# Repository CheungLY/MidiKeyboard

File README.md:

# MidiKeyboard
MidiKeyboard

This MIDI keyboard is meant to be a toy keyboard that will allow me to play most kinds of music.

The design of this is based off a basic keyboard, there are 8 keys for each of the 7 notes of an ionian scale with an extra tonic at the top
The aim is meant to be c-c with ionian in between but that can be programmed in firmware later

There is going to be a pitch bender and or modulation with the 2 dimensional joystick and octave jump up and down with instrument change and volume.

The chance to have a pitch bend with the joystick allows me to play more complex jazz tracks similar to the blues harmonica.

This is the schematic of the midi keyboard:

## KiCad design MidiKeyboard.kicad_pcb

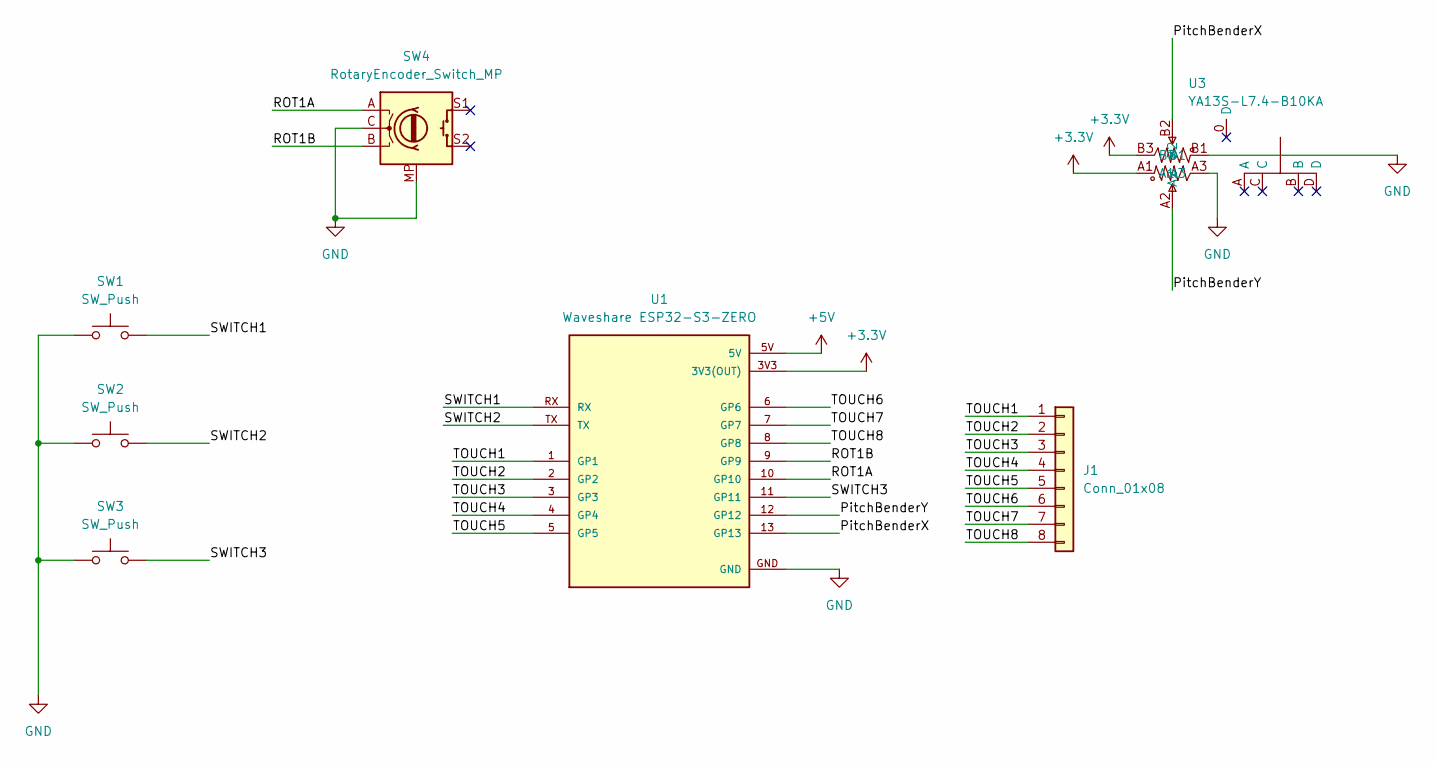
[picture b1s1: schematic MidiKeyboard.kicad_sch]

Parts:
J1: Conn_01x08; CapKeysMidi
SW1, SW2, SW3: SW_Push; Kailh Choc Low-Profile Switches
SW4: RotaryEncoder_Switch_MP; RotaryEncoder_Alps_EC11E-Switch_Vertical_H20mm
U1: Waveshare ESP32-S3-ZERO; Waveshare ESP32-S3-Zero; PARTREV NA
U3: YA13S-L7.4-B10KA; RES-ADJ-TH_YA13S-L7.4-B10KA-60-0-DL01; MPN YA13S-L7.4-B10Ka(60)-0-DL01; LCSC Part C37323748

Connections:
+3.3V: U1.3V3 (3V3(OUT)), U3.A1, U3.B3
+5V: U1.5V
/PitchBenderX: U1.13 (GP13), U3.B2
/PitchBenderY: U1.12 (GP12), U3.A2
/ROT1A: SW4.A, U1.10 (GP10)
/ROT1B: SW4.B, U1.9 (GP9)
/SWITCH1: SW1.2, U1.RX
/SWITCH2: SW2.2, U1.TX
/SWITCH3: SW3.2, U1.11 (GP11)
/TOUCH1: J1.1, U1.1 (GP1)
/TOUCH2: J1.2, U1.2 (GP2)
/TOUCH3: J1.3, U1.3 (GP3)
/TOUCH4: J1.4, U1.4 (GP4)
/TOUCH5: J1.5, U1.5 (GP5)
/TOUCH6: J1.6, U1.6 (GP6)
/TOUCH7: J1.7, U1.7 (GP7)
/TOUCH8: J1.8, U1.8 (GP8)
GND: SW1.1, SW2.1, SW3.1, SW4.C, SW4.MP, U1.GND, U3.A3, U3.B1

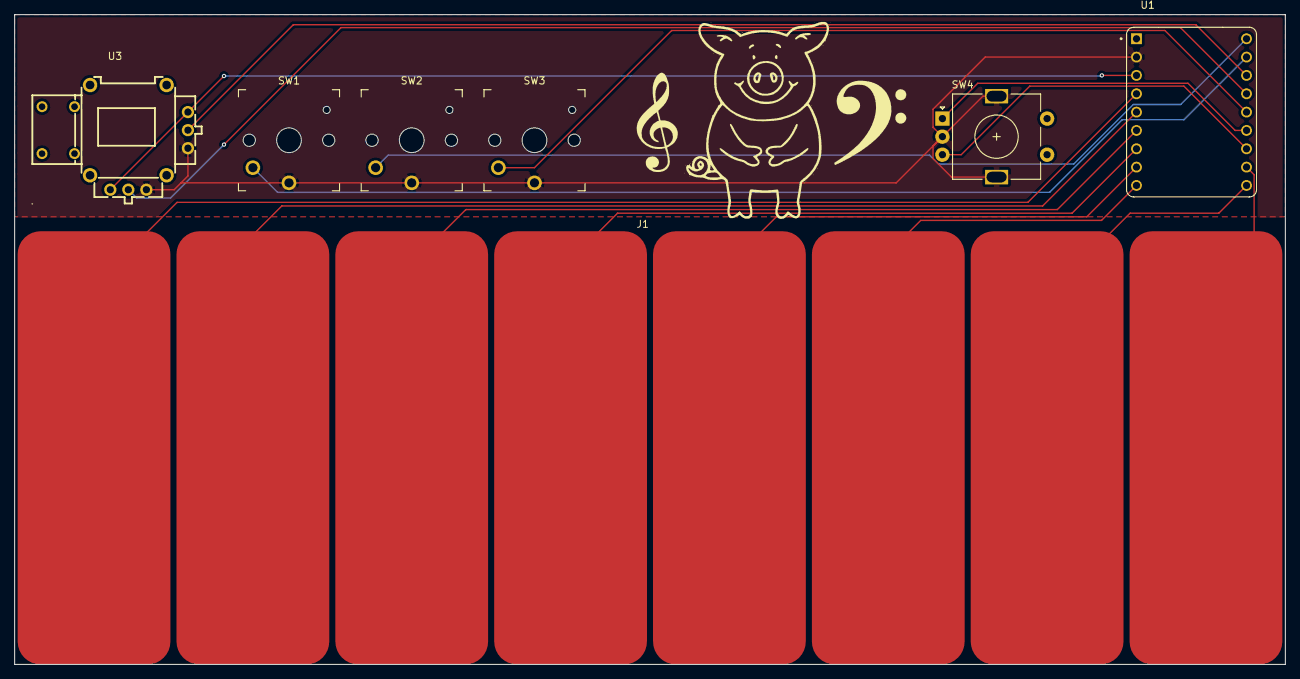
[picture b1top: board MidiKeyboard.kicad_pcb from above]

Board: 2 copper layers, 176.0 x 90.0 mm, 7 parts (0 on the bottom side), 17 nets.

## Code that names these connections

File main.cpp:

#include <Adafruit_TinyUSB.h>
#include <Encoder.h>

// =====================================================
// USB MIDI
// =====================================================

Adafruit_USBD_MIDI usb_midi;

// =====================================================
// TOUCH KEYS
// =====================================================

const uint8_t keyPins[8] =
{
  1,  // TOUCH1
  2,  // TOUCH2
  3,  // TOUCH3
  4,  // TOUCH4
  5,  // TOUCH5
  6,  // TOUCH6
  7,  // TOUCH7
  8   // TOUCH8
};

bool keyState[8];

const uint8_t noteMap[8] =
{
  60, // C4
  62, // D4
  64, // E4
  65, // F4
  67, // G4
  69, // A4
  71, // B4
  72  // C5
};

// =====================================================
// BUTTONS
// =====================================================

const int octaveDownPin = TX;   // SWITCH1
const int octaveUpPin   = RX;   // SWITCH2
const int programPin    = 11;   // SWITCH3

bool oldUp      = false;
bool oldDown    = false;
bool oldProgram = false;

// =====================================================
// ROTARY ENCODER
// =====================================================

const int encoderA = 10;   // ROT1A
const int encoderB = 9;    // ROT1B

Encoder encoder(encoderA, encoderB);

long lastEncoderValue = 0;
uint8_t volumeValue = 100;

// =====================================================
// JOYSTICK
// =====================================================

// Vertical axis -> Pitch Bend
const int pitchPin = 13;

// Horizontal axis -> Modulation Wheel
const int modPin = 12;

int lastPitch = 8192;
int lastModulation = -1;

// =====================================================
// MIDI STATE
// =====================================================

int octaveOffset = 0;
uint8_t currentProgram = 0;

// =====================================================
// MIDI HELPERS
// =====================================================

void sendNoteOn(uint8_t note)
{
  uint8_t msg[3] =
  {
    0x90,
    note,
    127
  };

  usb_midi.write(msg, 3);
}

void sendNoteOff(uint8_t note)
{
  uint8_t msg[3] =
  {
    0x80,
    note,
    0
  };

  usb_midi.write(msg, 3);
}

void sendControlChange(uint8_t cc,
                       uint8_t value)
{
  uint8_t msg[3] =
  {
    0xB0,
    cc,
    value
  };

  usb_midi.write(msg, 3);
}

void sendProgramChange(uint8_t program)
{
  uint8_t msg[2] =
  {
    0xC0,
    program
  };

  usb_midi.write(msg, 2);
}

void sendPitchBend(int value)
{
  value = constrain(value, 0, 16383);

  uint8_t lsb = value & 0x7F;
  uint8_t msb = (value >> 7) & 0x7F;

  uint8_t msg[3] =
  {
    0xE0,
    lsb,
    msb
  };

  usb_midi.write(msg, 3);
}

// =====================================================
// SETUP
// =====================================================

void setup()
{
  TinyUSBDevice.begin();

  for(int i = 0; i < 8; i++)
  {
    pinMode(keyPins[i], INPUT_PULLUP);
  }

  pinMode(octaveUpPin, INPUT_PULLUP);
  pinMode(octaveDownPin, INPUT_PULLUP);
  pinMode(programPin, INPUT_PULLUP);

  analogReadResolution(12);
}

// =====================================================
// KEYS
// =====================================================

void updateKeys()
{
  for(int i = 0; i < 8; i++)
  {
    bool pressed = !digitalRead(keyPins[i]);

    if(pressed && !keyState[i])
    {
      sendNoteOn(
        noteMap[i] + octaveOffset
      );
    }

    if(!pressed && keyState[i])
    {
      sendNoteOff(
        noteMap[i] + octaveOffset
      );
    }

    keyState[i] = pressed;
  }
}

// =====================================================
// BUTTONS
// =====================================================

void updateButtons()
{
  bool up =
    !digitalRead(octaveUpPin);

  bool down =
    !digitalRead(octaveDownPin);

  bool prog =
    !digitalRead(programPin);

  if(up && !oldUp)
  {
    octaveOffset += 12;

    if(octaveOffset > 48)
      octaveOffset = 48;
  }

  if(down && !oldDown)
  {
    octaveOffset -= 12;

    if(octaveOffset < -48)
      octaveOffset = -48;
  }

  if(prog && !oldProgram)
  {
    currentProgram++;

    if(currentProgram > 127)
      currentProgram = 0;

    sendProgramChange(currentProgram);
  }

  oldUp      = up;
  oldDown    = down;
  oldProgram
